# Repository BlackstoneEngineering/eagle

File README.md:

eagle
=====

Eagle CAD PCB Library &amp; Boards

Eagle Library Contains:<br>
-Stellaris Launchpad XL Header (EK-LM4F120XL, EK-TM4C123G)<br>
-Stellaris EM Header (SensorHub Booster Pack)<br>
-XBee S1/Pro Symbol,Package,Device <br>

Eagle Project Files:<br>
-XBee S1 / Pro Blizzard Class Launchpad BoosterPack: UART1 connected to XBee, other pins broken out with optional jumpers. <br>

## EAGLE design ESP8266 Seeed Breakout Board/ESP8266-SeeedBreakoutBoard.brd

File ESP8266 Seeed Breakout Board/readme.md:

## Description
This directory contains 2 breakout board designs for the ESP8266-01 wifi module. They are aptly named the breakout board and the breakout board minimal. The only real difference is the inclusion of a hardware reset line on the full board. Both boards are meant to be used with the Seeed Grove system. I have chosen this system because of its ease of use at events and for rapid prototyping. It involves no soldering, all the sensors have pre-written libraries, and the mbed.org ecosystem fully supports it. 

#### Full breakout board
This board is the more fully functional of the two and includes a hardware reset line and reset button. The main features are
* hardware reset button / digital I/O line
* two Seeed Grove connectors
* Firmware Update jumper to put ESP chip into firmware update mode

#### Minimal breakout board
This board is minimized for size and ease of use. It uses only through hole parts. 
Features:
- minimal size (cost of less than 1$ per PCB when ordered through OSHPARK)
- TX/RX lines broken out to Seeed Grove Header
- Jumper for Firmware Update mode

Here you can see the Minimal breakout board schematic and board layout files

Here you can see the bare PCB -> assembled PCB -> PCB + ESP8266-01 chip.

Here you can see the board hooked up to a Seeed Grove shield for use

## Order your own
You can order these PCB's  from oshpark here : 
* [Minimal PCB Page](https://oshpark.com/shared_projects/CQHJGKSS)
* [Full PCB Page](https://oshpark.com/shared_projects/uuOL5hfV )

## Code
To program the boards you can either use a ton of th existing code, or you can take a look at the code i'm working on at [the ESP8266 mbed team page](https://developer.mbed.org/teams/ESP8266). We have examples on using the ESP8266 as a peripheral device over UART and on how to udate the firmware.

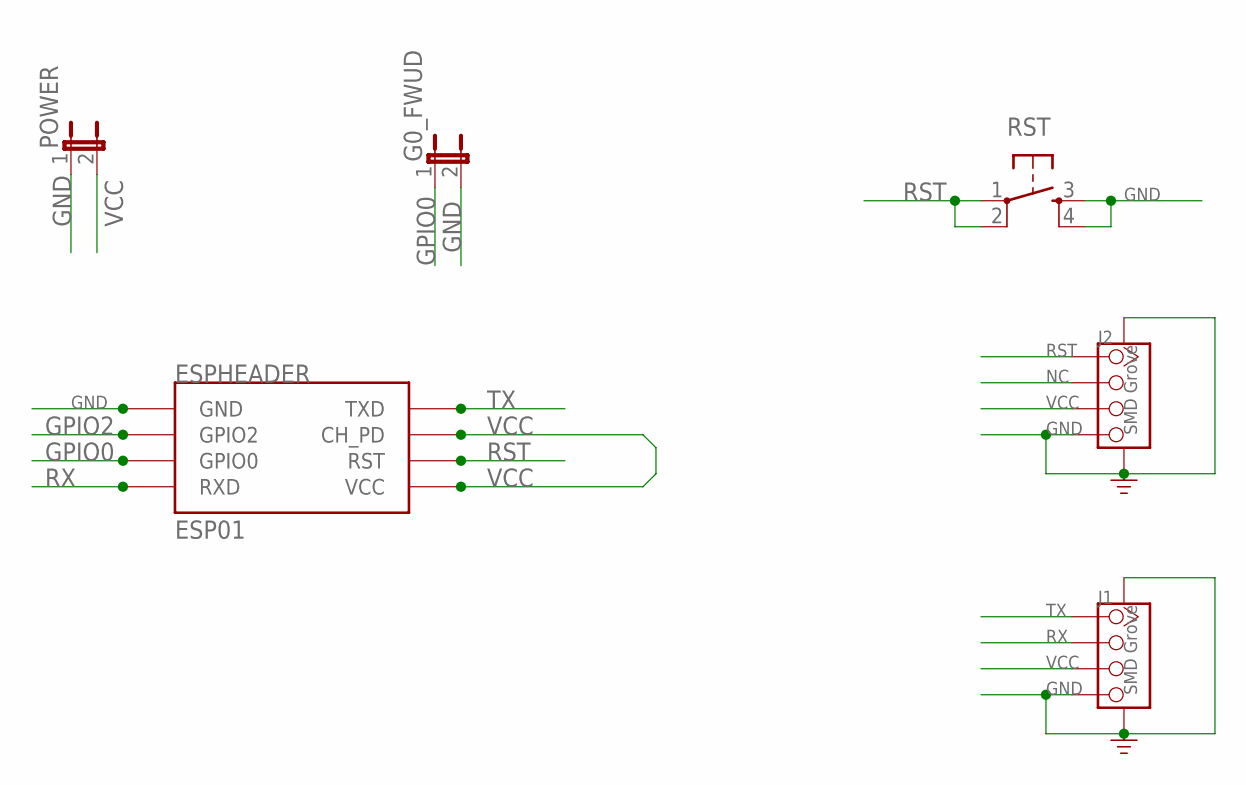
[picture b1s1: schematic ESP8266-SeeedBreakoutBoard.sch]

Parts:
ESPHEADER: ESP01
G0_FWUD: JUMPER-2PTH; 1X02
J1, J2: SMD Grove; 4P-SMD-2.0
POWER: JUMPER-2PTH; 1X02
RST: TAC_SWITCHPTH; TACTILE-PTH

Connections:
GND: ESPHEADER.GND, G0_FWUD.2, J1.4, J1.SS1, J1.SS2, J2.4, J2.SS1, J2.SS2, POWER.1, RST.3, RST.4
GPIO0: ESPHEADER.GPIO0, G0_FWUD.1
GPIO2: ESPHEADER.GPIO2
NC: J2.2
RST: ESPHEADER.RST, J2.1, RST.1, RST.2
RX: ESPHEADER.RX (RXD), J1.2
TX: ESPHEADER.TX (TXD), J1.1
VCC: ESPHEADER.CH_PD, ESPHEADER.VCC, J1.3, J2.3, POWER.2

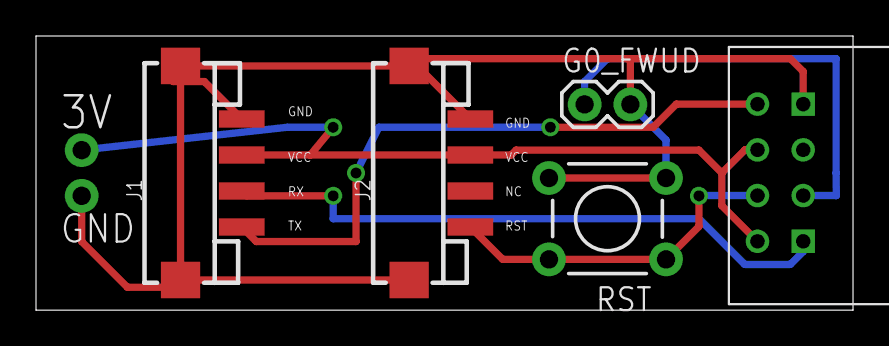
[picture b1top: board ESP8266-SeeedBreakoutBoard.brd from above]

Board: 2 copper layers, 45.4 x 15.2 mm, 6 parts (1 on the bottom side), 6 nets.

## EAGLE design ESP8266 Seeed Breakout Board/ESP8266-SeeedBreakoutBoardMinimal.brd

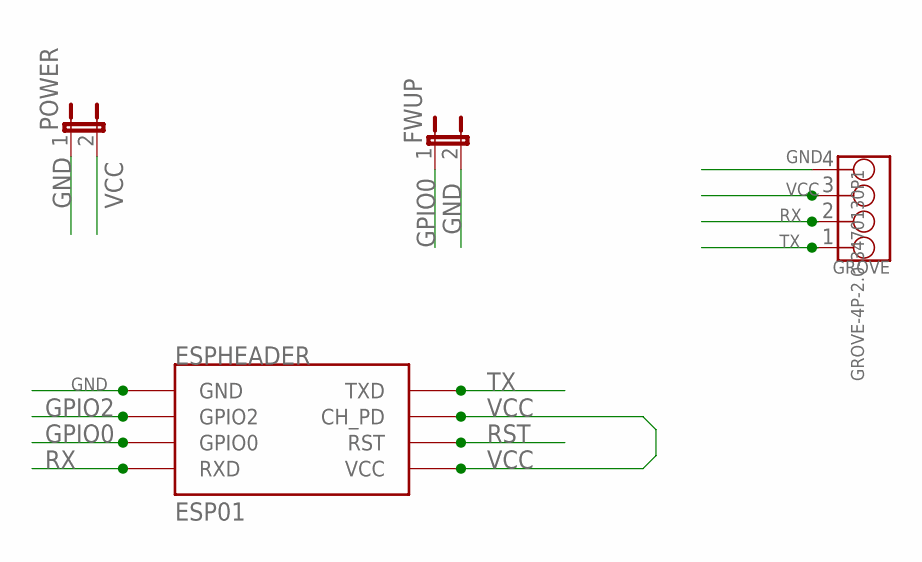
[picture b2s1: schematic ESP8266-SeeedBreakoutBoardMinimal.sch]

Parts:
ESPHEADER: ESP01
FWUP: JUMPER-2PTH; 1X02
GROVE: GROVE-4P-2.0-3470130P1; 4P-2.0
POWER: JUMPER-2PTH; 1X02

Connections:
GND: ESPHEADER.GND, FWUP.2, GROVE.4, POWER.1
GPIO0: ESPHEADER.GPIO0, FWUP.1
GPIO2: ESPHEADER.GPIO2
RST: ESPHEADER.RST
RX: ESPHEADER.RX (RXD), GROVE.2
TX: ESPHEADER.TX (TXD), GROVE.1
VCC: ESPHEADER.CH_PD, ESPHEADER.VCC, GROVE.3, POWER.2

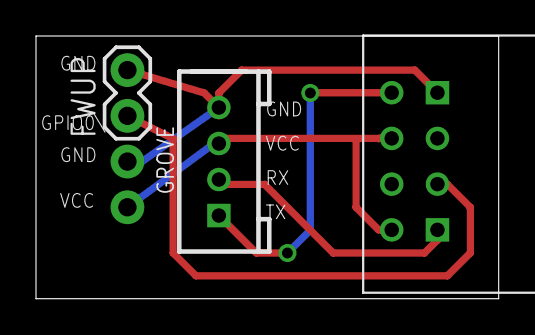
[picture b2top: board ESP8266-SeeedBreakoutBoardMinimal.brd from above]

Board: 2 copper layers, 25.7 x 14.6 mm, 4 parts (1 on the bottom side), 5 nets.

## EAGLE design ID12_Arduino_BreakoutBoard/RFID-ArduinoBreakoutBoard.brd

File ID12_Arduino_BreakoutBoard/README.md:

#ID12_Arduino_BreakoutBoard

## Overview
This board is a simple breakout board for the [ID12 RFID sensor](https://www.sparkfun.com/products/11827) to Arduino headers. 

## Details
All pins are broken out to jumpers so the board can be used by default in reader mode or can be configured for full use of the chip. For funsies a TMS36 Analog Temperature sensor was thrown in. It can be populated or not. Make sure to use the proper capacitors if you do populate it. 

The [sparkfun eagle libraries](https://github.com/sparkfun/SparkFun-Eagle-Libraries) were used for the base header outline and the ID12 footprint. 

## Pictures
The following are pictures of both the schamic and the finished product. 

Schematic

Board Layout<br>

Finished Product

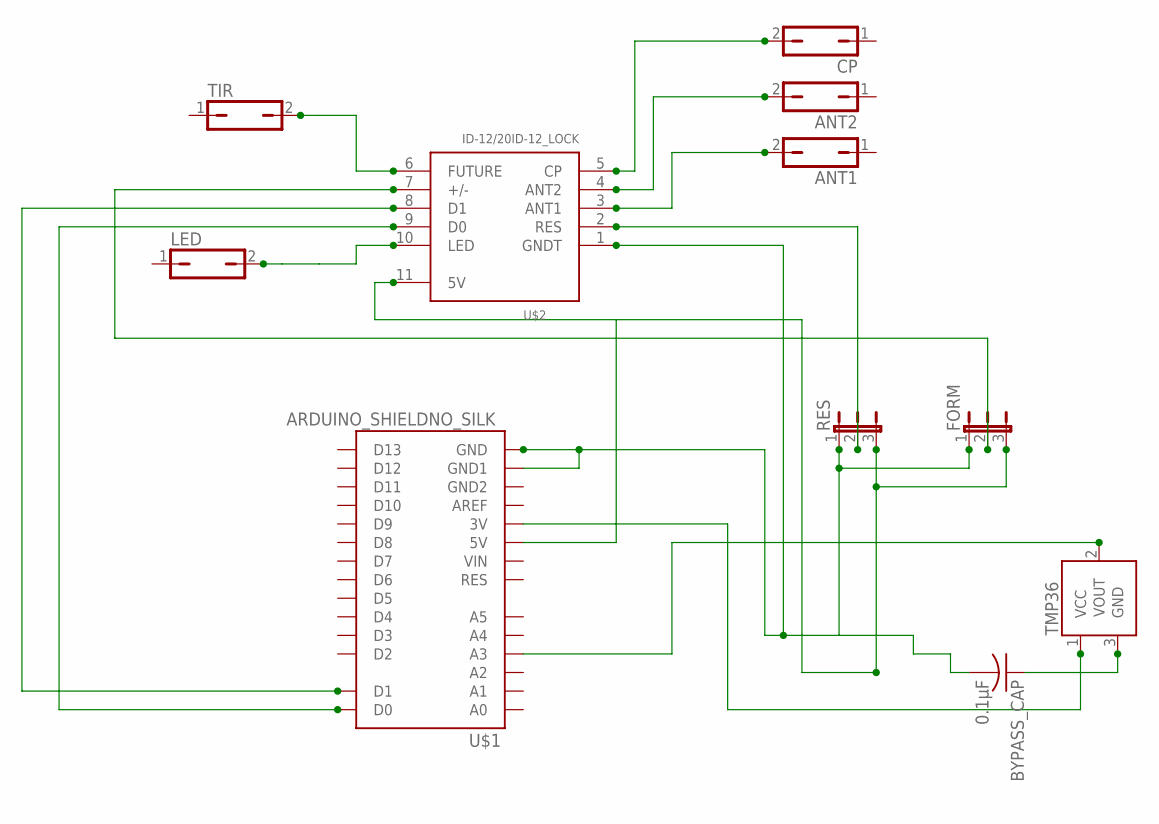
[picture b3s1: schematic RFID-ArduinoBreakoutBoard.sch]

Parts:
ANT1, ANT2: JP1Q; JP1
BYPASS_CAP: 0.1μF; C0805
CP: JP1Q; JP1
FORM: JP2W
LED: JP1Q; JP1
RES: JP2W
TIR: JP1Q; JP1
TMP36: TMP36GT9; TO-92
U$1: ARDUINO_SHIELDNO_SILK; DUEMILANOVE_VIAS
U$2: ID-12/20ID-12_LOCK; ID-12_LOCK

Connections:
5V: FORM.3, RES.3, U$1.5V, U$2.11 (5V)
D0: U$1.D0, U$2.9 (D0)
GND: BYPASS_CAP.2, FORM.1, RES.1, U$1.GND, U$1.GND1, U$2.1 (GNDT)
unnamed: TMP36.2 (VOUT), U$1.A3
unnamed: U$1.D1, U$2.8 (D1)
unnamed: TMP36.1 (VCC), U$1.3.3V (3V)
unnamed: BYPASS_CAP.1, TMP36.3 (GND)
RFID_ANT1: ANT1.2, U$2.3 (ANT1)
RFID_ANT2: ANT2.2, U$2.4 (ANT2)
RFID_CP: CP.2, U$2.5 (CP)
RFID_FORM: FORM.2, U$2.7 (+/-)
RFID_FUTURE: TIR.2, U$2.6 (FUTURE)
RFID_LED: LED.2, U$2.10 (LED)
RFID_RESET: RES.2, U$2.2 (RES)

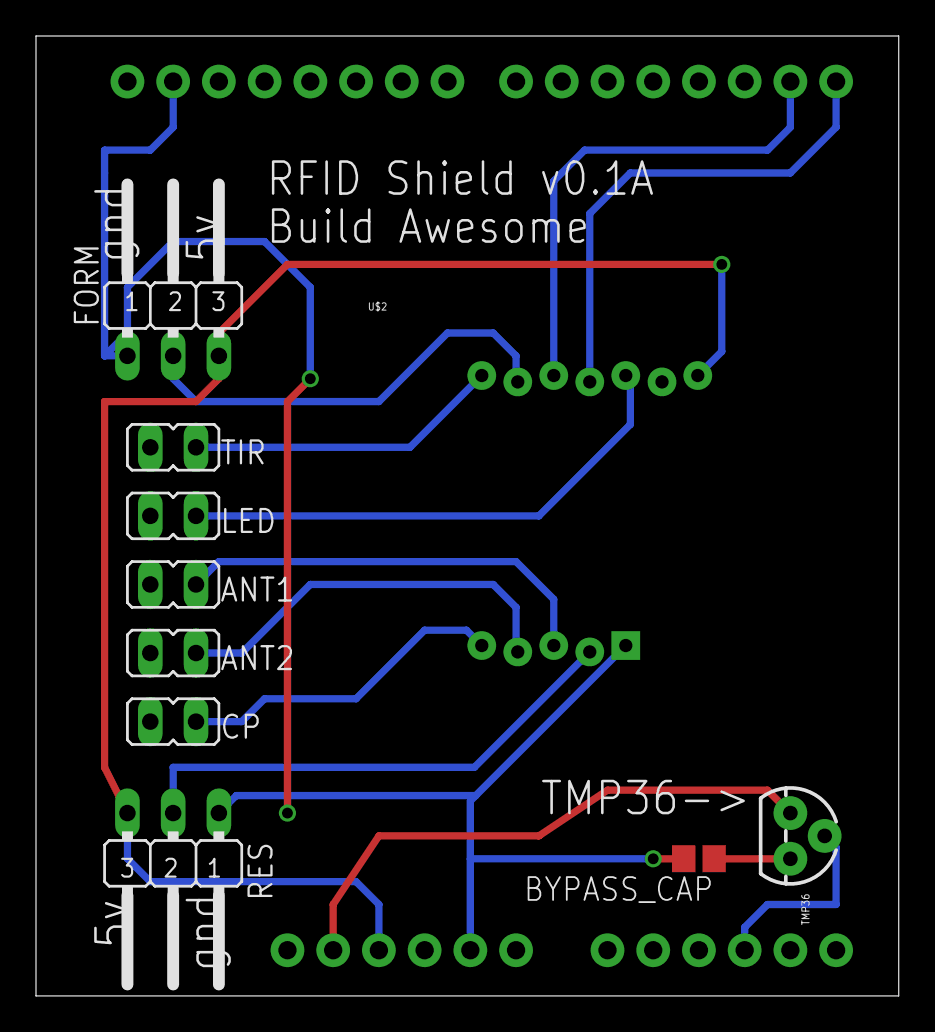
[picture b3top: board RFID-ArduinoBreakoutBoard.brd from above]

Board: 2 copper layers, 47.9 x 53.3 mm, 11 parts (0 on the bottom side), 14 nets.

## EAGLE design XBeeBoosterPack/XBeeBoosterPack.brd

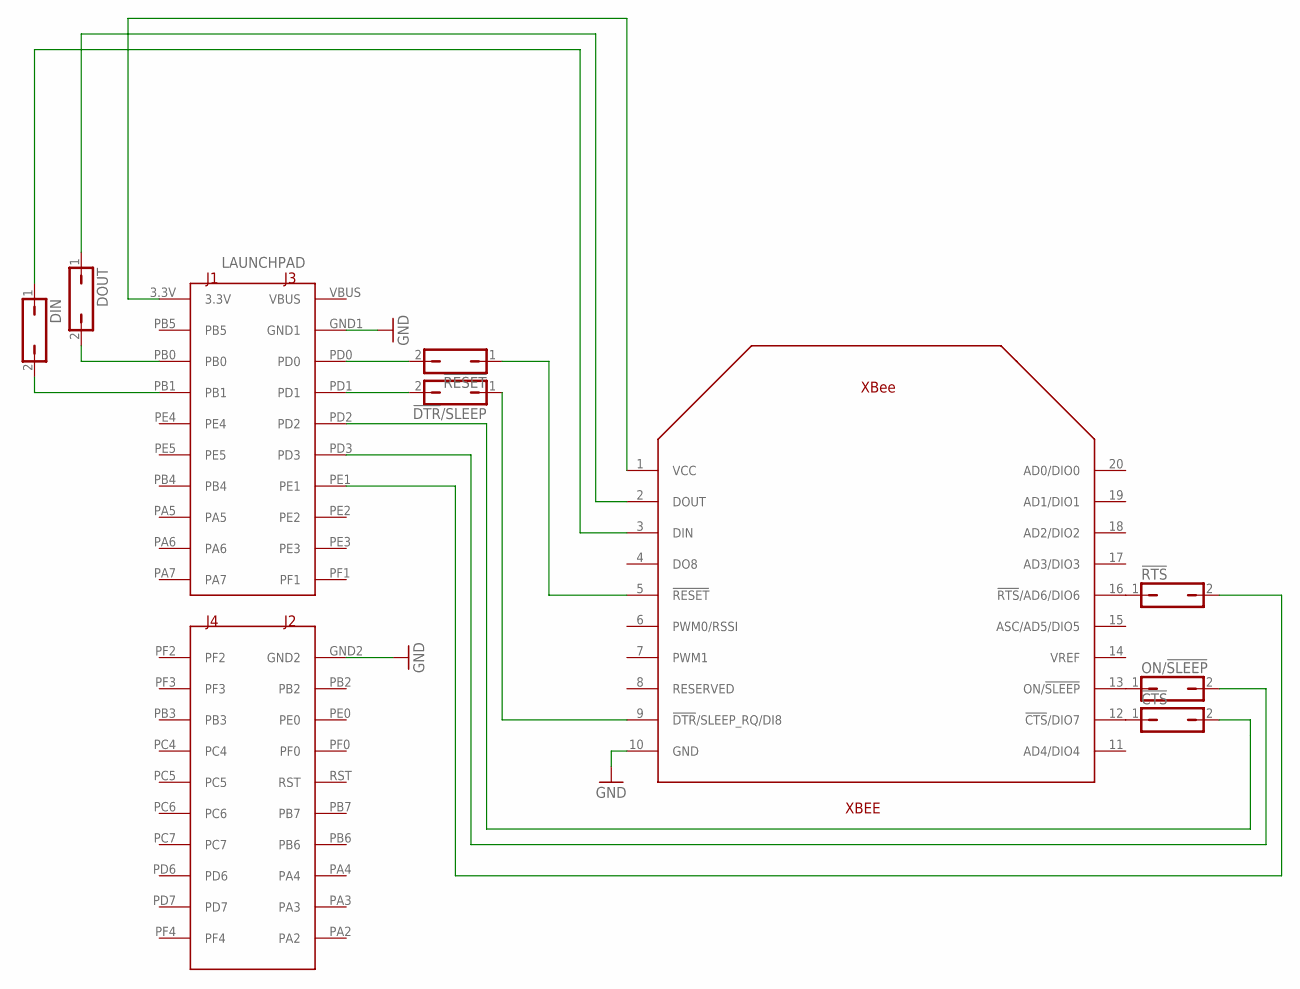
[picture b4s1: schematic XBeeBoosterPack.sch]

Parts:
!CTS!: JP1Q; JP1
!DTR!/SLEEP: JP1Q; JP1
!RESET: JP1Q; JP1
!RTS!: JP1Q; JP1
DIN: JP1Q; JP1
DOUT: JP1Q; JP1
LAUNCHPAD: STELLARIS_LAUNCHPAD_BLIZZARD_XL_HEADERS; STELLARISLAUNCHPADHEADERS
ON/!SLEEP!: JP1Q; JP1
XBEE: XBEE_HEADERS

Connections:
GND: LAUNCHPAD.GND1, LAUNCHPAD.GND2, XBEE.10 (GND)
unnamed: DOUT.1, XBEE.2 (DOUT)
unnamed: LAUNCHPAD.3.3V, XBEE.1 (VCC)
unnamed: DOUT.2, LAUNCHPAD.PB0
unnamed: DIN.1, XBEE.3 (DIN)
unnamed: DIN.2, LAUNCHPAD.PB1
unnamed: !RESET.2, LAUNCHPAD.PD0
unnamed: !RESET.1, XBEE.5 (!RESET)
unnamed: !DTR!/SLEEP.2, LAUNCHPAD.PD1
unnamed: !DTR!/SLEEP.1, XBEE.9 (!DTR!/SLEEP_RQ/DI8)
unnamed: !RTS!.1, XBEE.16 (!RTS!/AD6/DIO6)
unnamed: ON/!SLEEP!.1, XBEE.13 (ON/!SLEEP!)
unnamed: !CTS!.1, XBEE.12 (!CTS!/DIO7)
unnamed: !CTS!.2, LAUNCHPAD.PD2
unnamed: LAUNCHPAD.PD3, ON/!SLEEP!.2
unnamed: !RTS!.2, LAUNCHPAD.PE1
RST: LAUNCHPAD.RST
VBUS: LAUNCHPAD.VBUS

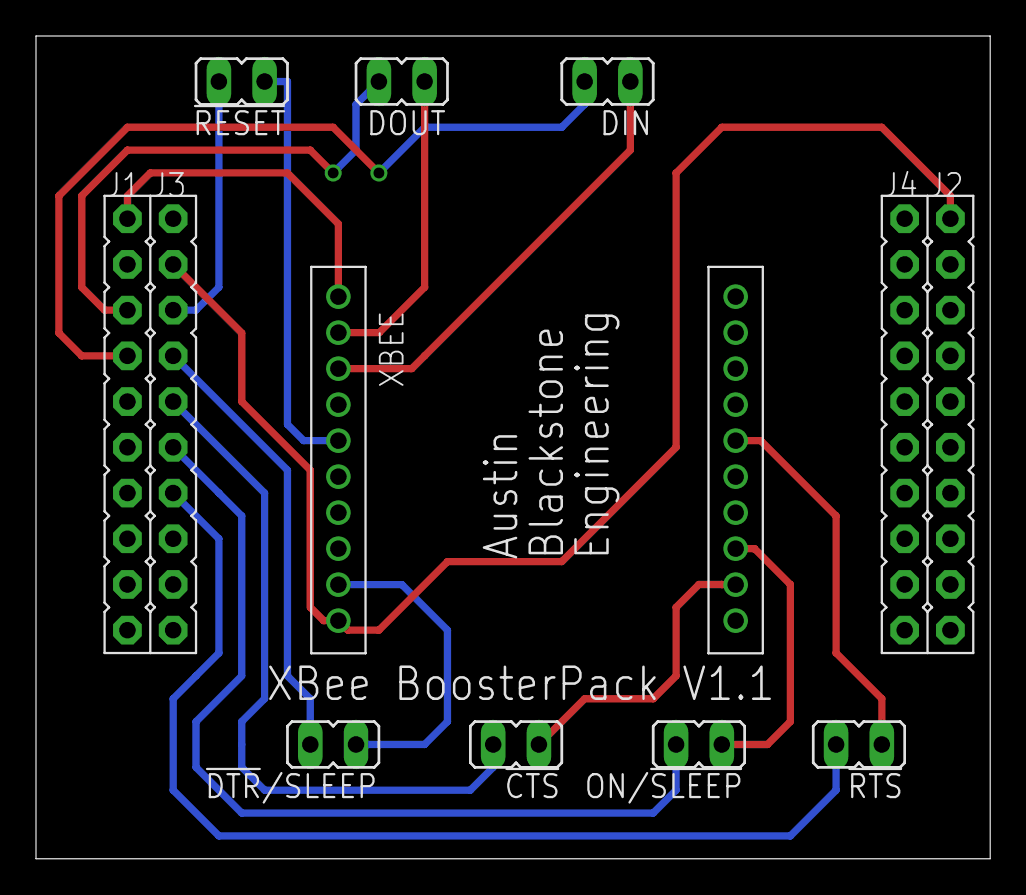
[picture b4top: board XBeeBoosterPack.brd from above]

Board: 2 copper layers, 53.0 x 45.7 mm, 9 parts (0 on the bottom side), 16 nets.

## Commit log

2013-07-26 this is a test commit to see if everything is working correctly on my side
2013-07-26 added public library
2013-07-26 removing junk files
2013-08-02 Added Stellaris EM Header Devices
2013-08-02 Update README.md
    added Stellaris Launchpad XL Headers and EM Headers
2013-08-08 Added XBee symbol, package, and device
2013-08-08 Add XBee Booster Pack Project
2013-08-08 add XBee project folder
2013-08-08 Add XBee BoosterPack Project.
2013-08-08 Added description to readme.md
2013-08-28 V1.1, changed name to boosterpack, added picture
2014-10-09 Arduino Header compatible breakout board for ID12 RFID reader. Complete project including gerbers, eagle files, .png of board and schematic, and pictures of finished product
2014-10-09 adding readme file to ID12 project
2014-10-09 updated readme file with formatting
2014-10-09 added pictures
2014-10-09 playing around with images
2014-10-09 still messing with images
2015-05-11 Adding ESP8266-01 Breakout board
2015-05-11 added pictures and readme
2015-05-11 removed large number of jpgs that bloated size of directory
2015-05-11 adding lower resolution images

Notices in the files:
parts and their libraries:
SparkFun-Retired: Licensing:Creative Commons ShareAlike 4.0 International - https://creativecommons.org/licenses/by-sa/4.0
